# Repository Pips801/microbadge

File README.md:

# Microbadge
Do you find Minibadges too big? Do you want to go even smaller? Try out the Microbadge! A minibadge can hold 6 of them!

The Microbadge is a 6mm x 6mm badge that uses 1.00mm pin headers to connect to a carrier board.
# Version 2! Do not use V1 anymore!
The Microbadge has been updated to V2 to support I2C, 1.00mm pins, and an additional 2x PROG pins for programming.  The microbadge has shrunk from 6.9mm to 6mm, and is small enough that you can fit 6 on a minibadge.

# Pictures

There are two Microbadge types - Simple and Full. Simple exposes +VBATT, CLK, 3x GND, and 2x +3v. The Full Microbadge adds two programming pins, and I2C SDA and SCL.

 # Importing into Kicad
 1. From the **Project Viewer**, **Symbol Editor** or the **Schematic Editor**, select **Preferences** > **Manage Symbol Libraries...** 

 2. Under **Global Libraries**, click **Add Existing Library to Table**, Select the `Microbadge V2.kicad-sym` file. I personally put it in `Documents\KiCad\{version}\symbols` on Windows, there's an equivalent folder on Mac and Linux as well.
 3. From the **Project Viewer**, **Footprint Editor**, or **PCB Editor**, select **Preferences** > **Manage Footprint Libraries...** 

 4. Under **Global Libraries**, click **Add Existing**, Select the `Microbadge V2.pretty` folder. I personally put it in `Documents\KiCad\{version}\footprints` on Windows, there's an equivalent folder on Mac and Linux as well.

# Creating a Microbadge carrier board (Minibadge)
This assumes you already have the SAINTCON Minibadge footprints and symbols added to your libraries.
 1. Open the **Schematic Editor**, and import a Minibadge symbol and at least one Microbadge symbol.
 2. Atatch **Power Symbols** and **Global Labels** to the Minibadge symbol. If you want blinking, don't forget to connect CLK. 

 3. Atatch the same Symbols to each Microbadge symbol you created. Each symbol will be a microbadge socket. 

 4. Select **Assign Footprints** > Assign a **Minibadge Footprint** (`Minibadge_Simple`, `Minibadge_Full`) to the **Minibadge** (not a slot), and assign a **Microbadge socket** footprint to the **Microbadges**. 

 5. Do your schematic and PCB work. Add LEDs, resistors, and other components.

# Creating a Microbadge
 1. Open the Schematic editor, and import a Microbadge symbol.
 2. Atatch **Power Symbols** and **Global Labels** to the microbadge. If you want blinking, don't forget to connect **CLK**. 

 3. Wire up your LEDs, resistors, and other components you want to use.
 4. Select **Assign Footprints** > Assign a Microbadge footprint (Square or Round, **not** a Socket!) to the **Microbadge**
 5. Assign `0603` or `0201` sized components to your LEDs and resistors. You have very little space to work with, so the smaller, the better.
 6. Do your PCB routing, silkscreening, etc.

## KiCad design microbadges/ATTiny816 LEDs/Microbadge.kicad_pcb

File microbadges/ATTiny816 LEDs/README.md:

# ATTiny816 LED Microbadge
## Pictures

## Description
A fully-programmable RGB LED Microbadge.
Features:
 * Microbadge with MCU and LEDs
 * 4x WS2812B-1010 RGB LEDs controlled by the NeoPixel library
 * ATTiny 816 MCU (8KB flash) programmable via UPDI through the ArduinoIDE
 * Diode to prevent reverse-voltage issues

## Programming
 * Supply 5v, GND, and UPDI. UPDI programming port is the normally NC port next to the CLK pin. It has an arrow pointing to the pin on either side of the board.

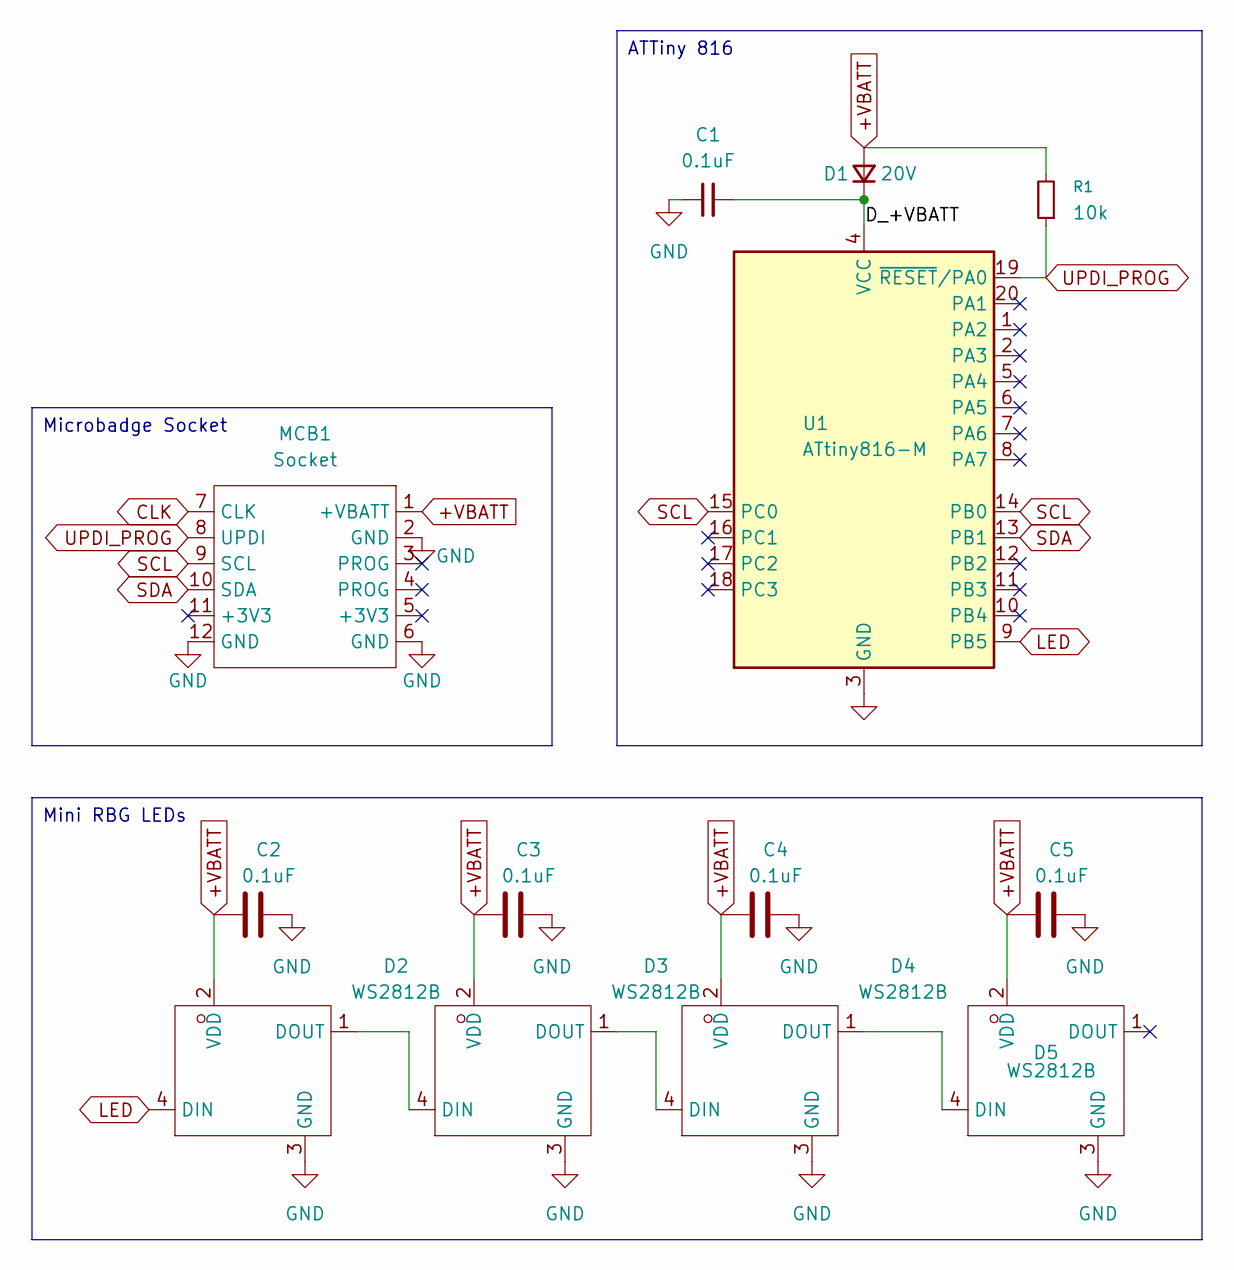
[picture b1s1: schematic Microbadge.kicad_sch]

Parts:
C1, C2, C3, C4, C5: 0.1uF; C_0201_0603Metric; LCSC Part # C49062
D1: 20V; D_0201_0603Metric; LCSC Part # C552803
D2, D3, D4, D5: WS2812B; LED-SMD_4P-L1.0-W1.0-TL_XL-1010RGBC-WS2812B; Manufacturer Part XL-1010RGBC-WS2812B; LCSC Part Name XL-1010RGBC-WS2812B
MCB1: Socket; Microbadge_V2_full_round
R1: 10k; R_0201_0603Metric; LCSC Part # C100126
U1: ATtiny816-M; VQFN-20-1EP_3x3mm_P0.4mm_EP1.7x1.7mm; LCSC Part # C2052778

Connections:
+VBATT: C2.1, C3.1, C4.1, C5.1, D1.2 (A), D2.2 (VDD), D3.2 (VDD), D4.2 (VDD), D5.2 (VDD), MCB1.1 (+VBATT), R1.2
/D_+VBATT: C1.2, D1.1 (K), U1.4 (VCC)
CLK: MCB1.7 (CLK)
GND: C1.1, C2.2, C3.2, C4.2, C5.2, D2.3 (GND), D3.3 (GND), D4.3 (GND), D5.3 (GND), MCB1.2 (GND), MCB1.6 (GND), MCB1.12 (GND), U1.3 (GND), U1.21 (GND)
LED: D2.4 (DIN), U1.9 (PB5)
unnamed: D2.1 (DOUT), D3.4 (DIN)
unnamed: D3.1 (DOUT), D4.4 (DIN)
unnamed: D4.1 (DOUT), D5.4 (DIN)
SCL: MCB1.9 (SCL), U1.14 (PB0), U1.15 (PC0)
SDA: MCB1.10 (SDA), U1.13 (PB1)
UPDI_PROG: MCB1.8 (UPDI), R1.1, U1.19 (~RESET/PA0)

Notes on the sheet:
Microbadge Socket
ATTiny 816
Mini RBG LEDs

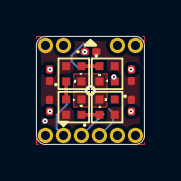
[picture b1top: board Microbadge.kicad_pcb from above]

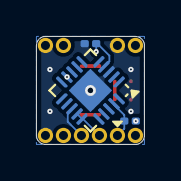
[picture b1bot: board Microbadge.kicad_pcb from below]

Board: 2 copper layers, 6.0 x 6.0 mm, 13 parts (3 on the bottom side), 10 nets.

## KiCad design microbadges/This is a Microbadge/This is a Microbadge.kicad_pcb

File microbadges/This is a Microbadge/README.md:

# This is MICROBADGE
## Pictures

## Description
A Microbadge, showing you what a Microbadge is.

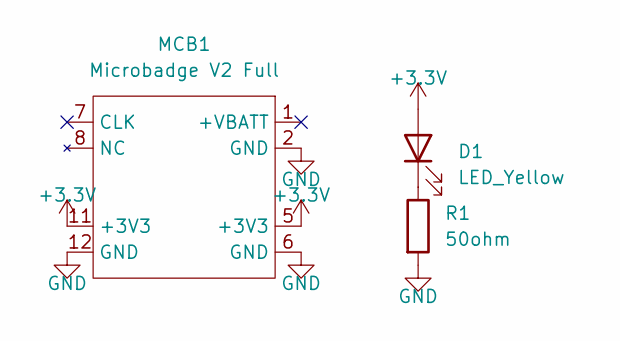
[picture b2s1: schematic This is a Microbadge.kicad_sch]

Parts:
D1: LED_Yellow; LED_0603_1608Metric; LCSC Part # C89811
MCB1: Microbadge V2 Full; Microbadge_V2_simple_round
R1: 50ohm; R_0402_1005Metric; LCSC Part # C25120

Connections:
+3.3V: D1.2 (A), MCB1.5 (+3V3), MCB1.11 (+3V3)
GND: MCB1.2 (GND), MCB1.6 (GND), MCB1.12 (GND), R1.2
unnamed: D1.1 (K), R1.1

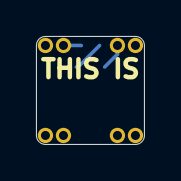
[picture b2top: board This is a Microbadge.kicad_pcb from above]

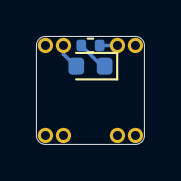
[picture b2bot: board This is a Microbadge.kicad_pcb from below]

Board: 2 copper layers, 6.0 x 6.0 mm, 3 parts (2 on the bottom side), 3 nets.

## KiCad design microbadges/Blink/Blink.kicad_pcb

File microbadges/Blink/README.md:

# BLINK Microbadge
## Pictures

## Description
A microbadge that uses the CLK pin to Blink

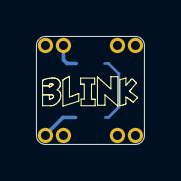
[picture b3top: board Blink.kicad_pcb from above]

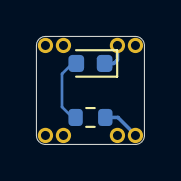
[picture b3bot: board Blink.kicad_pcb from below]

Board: 2 copper layers, 6.0 x 6.0 mm, 3 parts (2 on the bottom side), 3 nets.

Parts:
D1: LED; LED_0603_1608Metric
MCB1: Microbadge V2 Full; Microbadge_V2_simple_round
R1: R; R_0603_1608Metric

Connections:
CLK: MCB1.7 (CLK), R1.1
GND: D1.1 (K), MCB1.2 (GND), MCB1.6 (GND), MCB1.12 (GND)
unnamed: D1.2 (A), R1.2

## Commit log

2025-07-25 Add ATTiny Microbadge
2025-07-25 Add Schematic PDF
2025-07-25 Add arrows for direction and UPDI Programming
2025-07-25 add pannelization settings 8x8
2025-07-25 Add panelization files
2025-07-25 move to folder
2025-07-25 rename
2025-07-28 Update ATTiny Voltage to use +VBATT instead of +3V3
2025-07-28 Fix label
2025-07-28 update schematic PDF
2025-07-28 Update to V2
2025-07-28 Update Microbadge to V2 design
2025-07-28 small changes
2025-07-28 rotate Resistor
2025-07-31 Add LCSC part numbers to components
2025-07-31 Update pictures
2025-07-31 update margins for LEDs
2025-07-31 Add Blink board
2025-07-31 Add this is MICROBADGE
2025-07-31 Update to Bit-banged I2C
2025-07-31 Update I2C pins
